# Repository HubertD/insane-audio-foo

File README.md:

insane-audio-foo
================

Portable Modular Digital Audio Mixer / Interface / Recorder with High Quality and stuff.

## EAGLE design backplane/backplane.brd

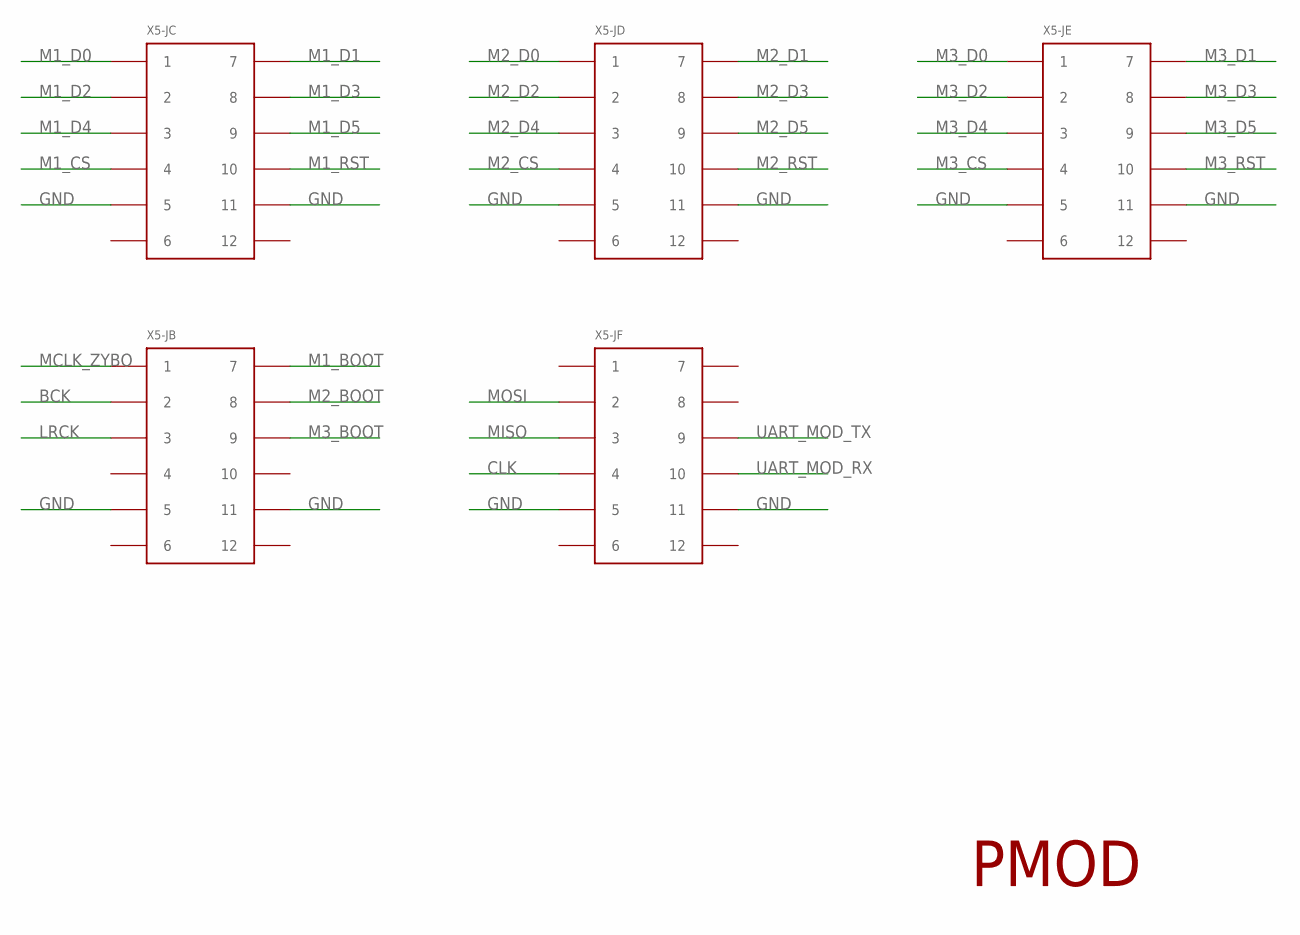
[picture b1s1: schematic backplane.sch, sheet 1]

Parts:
X5-JB, X5-JC, X5-JD, X5-JE, X5-JF: PINCON-2X6; PINCON-2X6-SMD

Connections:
BCK: X5-JB.P$2 (2); also elsewhere on the board
CLK: X5-JF.P$4 (4); also elsewhere on the board
GND: X5-JB.P$5 (5), X5-JB.P$11 (11), X5-JC.P$5 (5), X5-JC.P$11 (11), X5-JD.P$5 (5), X5-JD.P$11 (11), X5-JE.P$5 (5), X5-JE.P$11 (11), X5-JF.P$5 (5), X5-JF.P$11 (11); also elsewhere on the board
LRCK: X5-JB.P$3 (3); also elsewhere on the board
M1_BOOT: X5-JB.P$7 (7); also elsewhere on the board
M1_CS: X5-JC.P$4 (4); also elsewhere on the board
M1_D0: X5-JC.P$1 (1); also elsewhere on the board
M1_D1: X5-JC.P$7 (7); also elsewhere on the board
M1_D2: X5-JC.P$2 (2); also elsewhere on the board
M1_D3: X5-JC.P$8 (8); also elsewhere on the board
M1_D4: X5-JC.P$3 (3); also elsewhere on the board
M1_D5: X5-JC.P$9 (9); also elsewhere on the board
M1_RST: X5-JC.P$10 (10); also elsewhere on the board
M2_BOOT: X5-JB.P$8 (8); also elsewhere on the board
M2_CS: X5-JD.P$4 (4); also elsewhere on the board
M2_D0: X5-JD.P$1 (1); also elsewhere on the board
M2_D1: X5-JD.P$7 (7); also elsewhere on the board
M2_D2: X5-JD.P$2 (2); also elsewhere on the board
M2_D3: X5-JD.P$8 (8); also elsewhere on the board
M2_D4: X5-JD.P$3 (3); also elsewhere on the board
M2_D5: X5-JD.P$9 (9); also elsewhere on the board
M2_RST: X5-JD.P$10 (10); also elsewhere on the board
M3_BOOT: X5-JB.P$9 (9); also elsewhere on the board
M3_CS: X5-JE.P$4 (4); also elsewhere on the board
M3_D0: X5-JE.P$1 (1); also elsewhere on the board
M3_D1: X5-JE.P$7 (7); also elsewhere on the board
M3_D2: X5-JE.P$2 (2); also elsewhere on the board
M3_D3: X5-JE.P$8 (8); also elsewhere on the board
M3_D4: X5-JE.P$3 (3); also elsewhere on the board
M3_D5: X5-JE.P$9 (9); also elsewhere on the board
M3_RST: X5-JE.P$10 (10); also elsewhere on the board
MCLK_ZYBO: X5-JB.P$1 (1); also elsewhere on the board
MISO: X5-JF.P$3 (3); also elsewhere on the board
MOSI: X5-JF.P$2 (2); also elsewhere on the board
UART_MOD_RX: X5-JF.P$10 (10); also elsewhere on the board
UART_MOD_TX: X5-JF.P$9 (9); also elsewhere on the board

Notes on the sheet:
PMOD

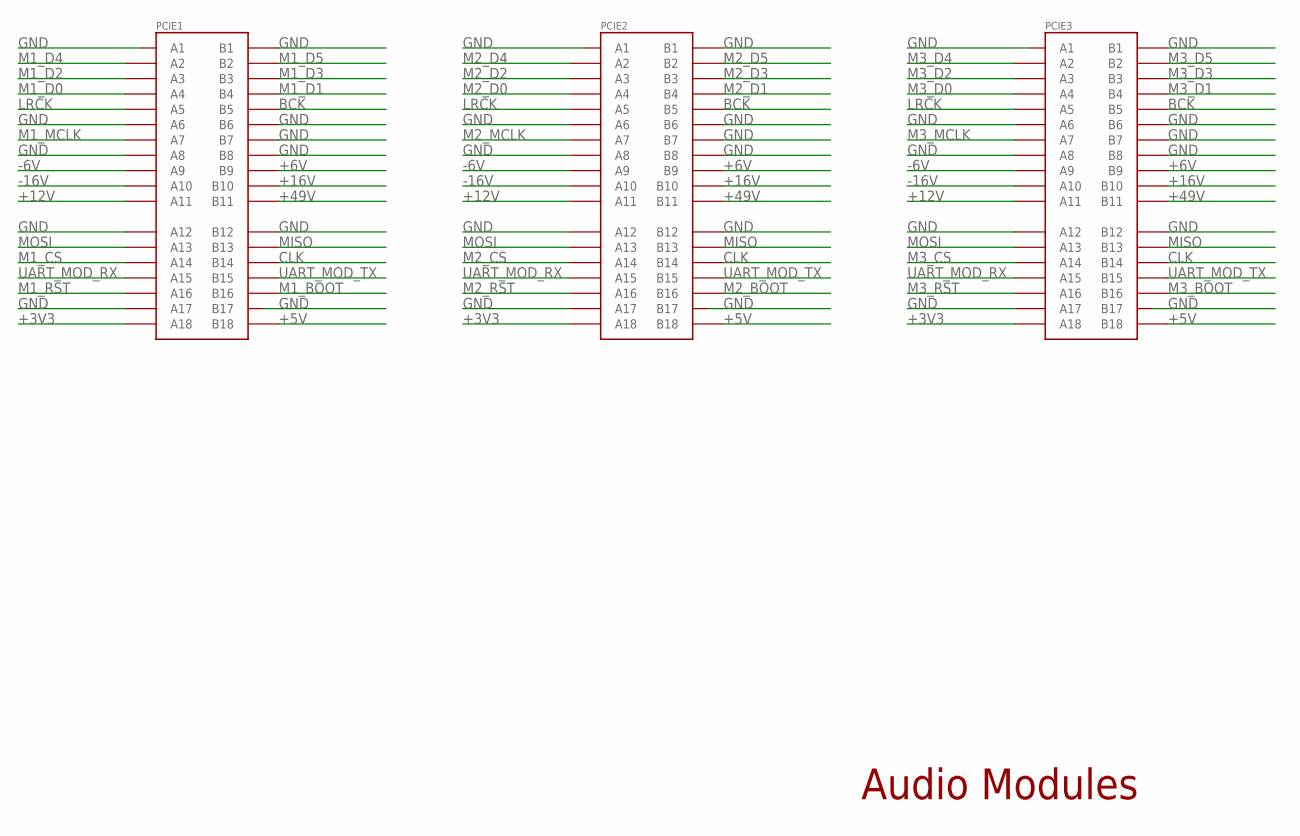
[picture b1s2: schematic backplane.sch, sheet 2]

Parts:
PCIE1, PCIE2, PCIE3: PCIE-36-SKT-SMD; FCI-10076266-100CLF

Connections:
+3V3: PCIE1.A18, PCIE2.A18, PCIE3.A18; also elsewhere on the board
+5V: PCIE1.B19 (B18), PCIE2.B19 (B18), PCIE3.B19 (B18); also elsewhere on the board
+6V: PCIE1.B9, PCIE2.B9, PCIE3.B9; also elsewhere on the board
+12V: PCIE1.A11, PCIE2.A11, PCIE3.A11; also elsewhere on the board
+16V: PCIE1.B10, PCIE2.B10, PCIE3.B10; also elsewhere on the board
+49V: PCIE1.B11, PCIE2.B11, PCIE3.B11; also elsewhere on the board
-6V: PCIE1.A9, PCIE2.A9, PCIE3.A9; also elsewhere on the board
-16V: PCIE1.A10, PCIE2.A10, PCIE3.A10; also elsewhere on the board
BCK: PCIE1.B5, PCIE2.B5, PCIE3.B5; also elsewhere on the board
CLK: PCIE1.B14, PCIE2.B14, PCIE3.B14; also elsewhere on the board
GND: PCIE1.A1, PCIE1.A6, PCIE1.A8, PCIE1.A12, PCIE1.A17, PCIE1.B1, PCIE1.B6, PCIE1.B7, PCIE1.B8, PCIE1.B12, PCIE1.B18 (B17), PCIE2.A1, PCIE2.A6, PCIE2.A8, PCIE2.A12, PCIE2.A17, PCIE2.B1, PCIE2.B6, PCIE2.B7, PCIE2.B8, PCIE2.B12, PCIE2.B18 (B17), PCIE3.A1, PCIE3.A6, PCIE3.A8, PCIE3.A12, PCIE3.A17, PCIE3.B1, PCIE3.B6, PCIE3.B7, PCIE3.B8, PCIE3.B12, PCIE3.B18 (B17); also elsewhere on the board
LRCK: PCIE1.A5, PCIE2.A5, PCIE3.A5; also elsewhere on the board
M1_BOOT: PCIE1.B16; also elsewhere on the board
M1_CS: PCIE1.A14; also elsewhere on the board
M1_D0: PCIE1.A4; also elsewhere on the board
M1_D1: PCIE1.B4; also elsewhere on the board
M1_D2: PCIE1.A3; also elsewhere on the board
M1_D3: PCIE1.B3; also elsewhere on the board
M1_D4: PCIE1.A2; also elsewhere on the board
M1_D5: PCIE1.B2; also elsewhere on the board
M1_MCLK: PCIE1.A7; also elsewhere on the board
M1_RST: PCIE1.A16; also elsewhere on the board
M2_BOOT: PCIE2.B16; also elsewhere on the board
M2_CS: PCIE2.A14; also elsewhere on the board
M2_D0: PCIE2.A4; also elsewhere on the board
M2_D1: PCIE2.B4; also elsewhere on the board
M2_D2: PCIE2.A3; also elsewhere on the board
M2_D3: PCIE2.B3; also elsewhere on the board
M2_D4: PCIE2.A2; also elsewhere on the board
M2_D5: PCIE2.B2; also elsewhere on the board
M2_MCLK: PCIE2.A7; also elsewhere on the board
M2_RST: PCIE2.A16; also elsewhere on the board
M3_BOOT: PCIE3.B16; also elsewhere on the board
M3_CS: PCIE3.A14; also elsewhere on the board
M3_D0: PCIE3.A4; also elsewhere on the board
M3_D1: PCIE3.B4; also elsewhere on the board
M3_D2: PCIE3.A3; also elsewhere on the board
M3_D3: PCIE3.B3; also elsewhere on the board
M3_D4: PCIE3.A2; also elsewhere on the board
M3_D5: PCIE3.B2; also elsewhere on the board
M3_MCLK: PCIE3.A7; also elsewhere on the board
M3_RST: PCIE3.A16; also elsewhere on the board
MISO: PCIE1.B13, PCIE2.B13, PCIE3.B13; also elsewhere on the board
MOSI: PCIE1.A13, PCIE2.A13, PCIE3.A13; also elsewhere on the board
UART_MOD_RX: PCIE1.A15, PCIE2.A15, PCIE3.A15; also elsewhere on the board
UART_MOD_TX: PCIE1.B15, PCIE2.B15, PCIE3.B15; also elsewhere on the board

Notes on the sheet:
Audio Modules

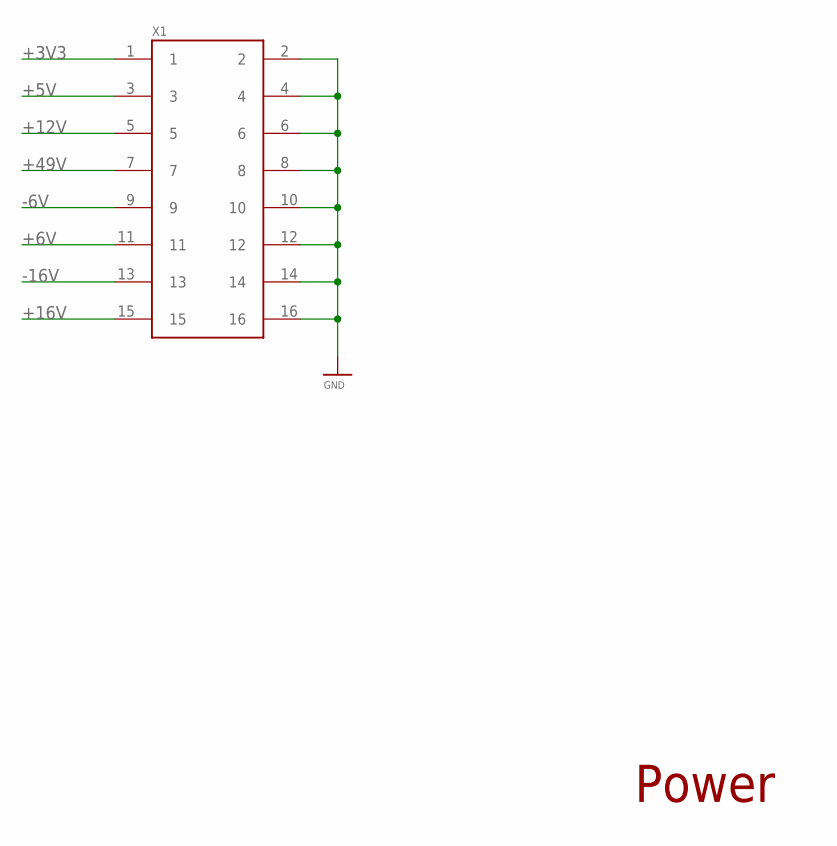
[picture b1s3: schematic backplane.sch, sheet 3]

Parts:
X1: PINCON-2X8

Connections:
+3V3: X1.1; also elsewhere on the board
+5V: X1.3; also elsewhere on the board
+6V: X1.11; also elsewhere on the board
+12V: X1.5; also elsewhere on the board
+16V: X1.15; also elsewhere on the board
+49V: X1.7; also elsewhere on the board
-6V: X1.9; also elsewhere on the board
-16V: X1.13; also elsewhere on the board
GND: X1.2, X1.4, X1.6, X1.8, X1.10, X1.12, X1.14, X1.16; also elsewhere on the board

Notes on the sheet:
Power

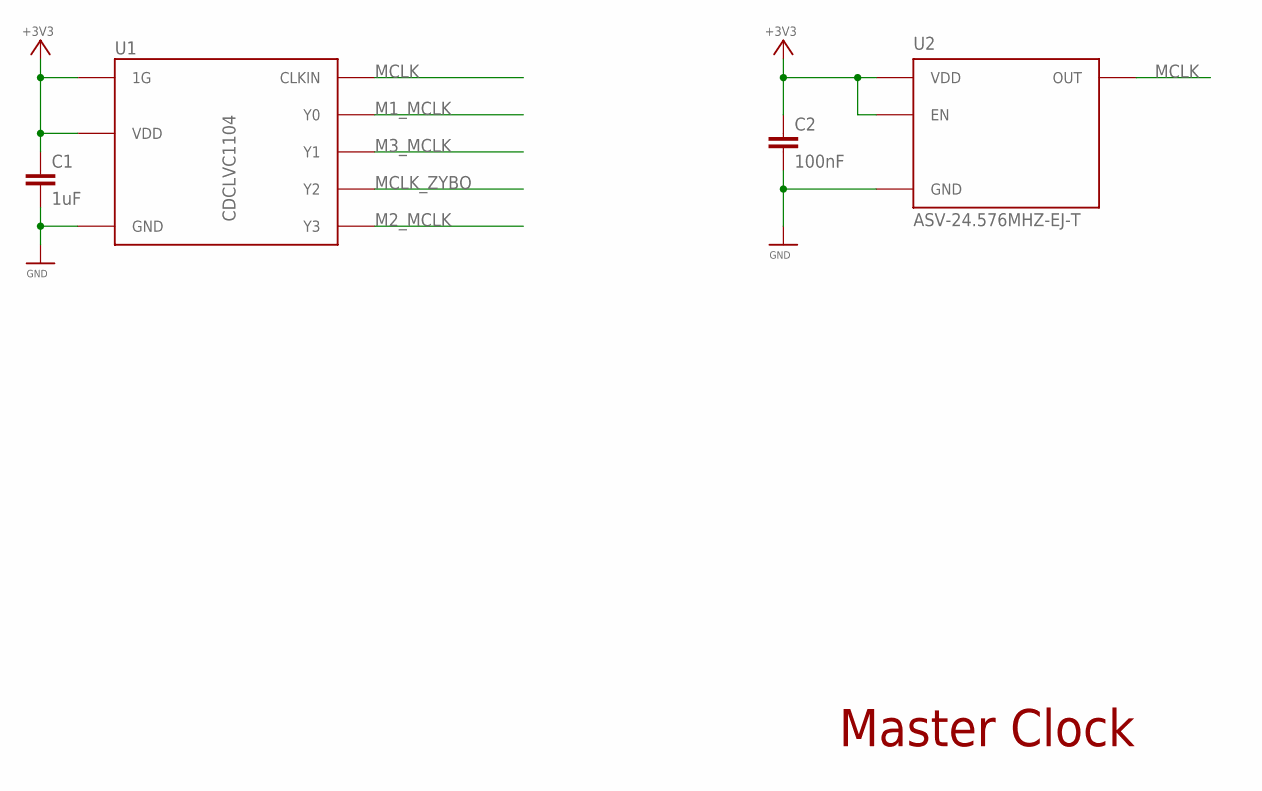
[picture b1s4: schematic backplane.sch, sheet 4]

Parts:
C1: 1uF; C0805
C2: 100nF; C0603
U1: CDCLVC1104; TSSOP8
U2: ASV-24.576MHZ-EJ-T; ABRACON_ASV; MPN ASV-24.576MHZ-EJ-T

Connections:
+3V3: C1.1, C2.1, U1.2 (1G), U1.6 (VDD), U2.1 (EN), U2.4 (VDD); also elsewhere on the board
GND: C1.2, C2.2, U1.4 (GND), U2.2 (GND); also elsewhere on the board
M1_MCLK: U1.3 (Y0); also elsewhere on the board
M2_MCLK: U1.7 (Y3); also elsewhere on the board
M3_MCLK: U1.8 (Y1); also elsewhere on the board
MCLK: U1.1 (CLKIN), U2.3 (OUT)
MCLK_ZYBO: U1.5 (Y2); also elsewhere on the board

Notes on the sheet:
Master Clock

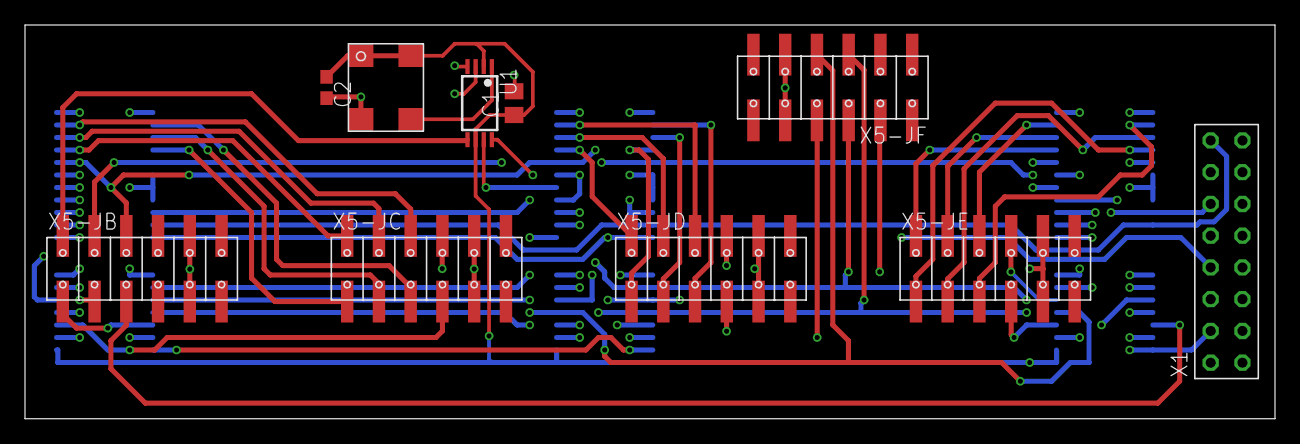
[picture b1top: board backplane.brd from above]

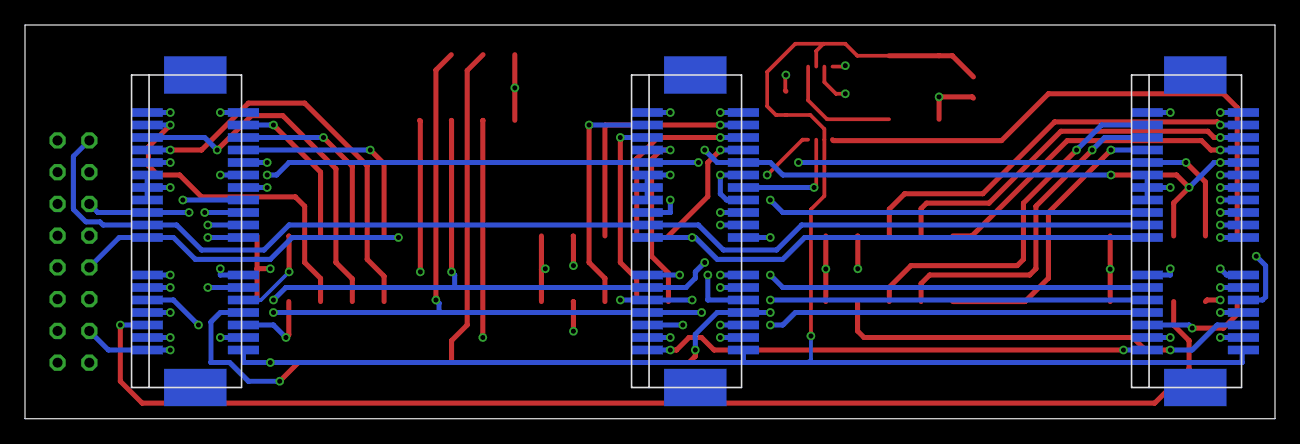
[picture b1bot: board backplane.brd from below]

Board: 4 copper layers, 100.0 x 31.5 mm, 13 parts (3 on the bottom side), 48 nets.

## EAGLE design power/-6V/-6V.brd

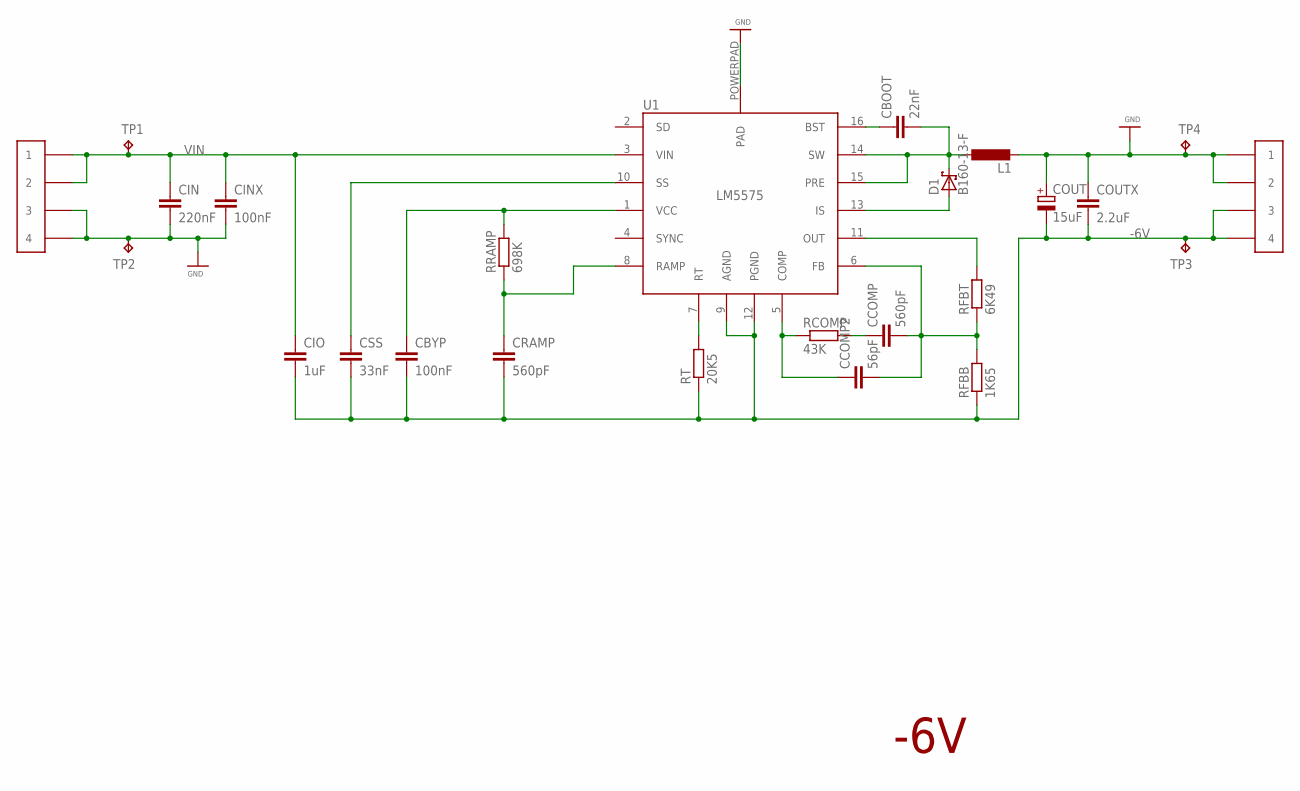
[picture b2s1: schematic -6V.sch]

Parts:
CBOOT: 22nF; C0603
CBYP: 100nF; C0603
CCOMP: 560pF; C0603
CCOMP2: 56pF; C0603
CIN: 220nF; C0805
CINX: 100nF; C0805
CIO: 1uF; C1206; MPN C3216X7R1H105K
COUT: 15uF; KEMET_EDK_5MM; MPN 10SVP15M
COUTX: 2.2uF; C0603; MPN GRM188R61A225KE34D
CRAMP: 560pF; C0603
CSS: 33nF; C0603
D1: B160-13-F; SMA
L1: LSDR1006; BOURNS-SDR1006; MPN SDR1006-560KL
RCOMP: 43K; R0603
RFBB: 1K65; R0603
RFBT: 6K49; R0603
RRAMP: 698K; R0603
RT: 20K5; R0603
TP1, TP2, TP3, TP4: TP; TESTPAD
U1: LM5575; HTSSOP16
X1, X2: PINCON-1X4

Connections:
-6V: CBYP.2, CIO.2, COUT.M (-), COUTX.2, CRAMP.2, CSS.2, RFBB.1, RT.1, TP3.P$1, U1.9 (AGND), U1.12 (PGND), X2.P$3 (3), X2.P$4 (4)
GND: CIN.2, CINX.2, COUT.P (+), COUTX.1, L1.2, TP2.P$1, TP4.P$1, U1.POWERPAD (PAD), X1.P$3 (3), X1.P$4 (4), X2.P$1 (1), X2.P$2 (2)
unnamed: CSS.1, U1.10 (SS)
unnamed: CBYP.1, RRAMP.2, U1.1 (VCC)
unnamed: CRAMP.1, RRAMP.1, U1.8 (RAMP)
unnamed: RT.2, U1.7 (RT)
unnamed: CCOMP2.1, RCOMP.1, U1.5 (COMP)
unnamed: CCOMP.1, RCOMP.2
unnamed: CCOMP.2, CCOMP2.2, RFBB.2, RFBT.1, U1.6 (FB)
unnamed: RFBT.2, U1.11 (OUT)
unnamed: D1.A, U1.13 (IS)
unnamed: CBOOT.2, D1.C, L1.1, U1.14 (SW), U1.15 (PRE)
unnamed: CBOOT.1, U1.16 (BST)
VIN: CIN.1, CINX.1, CIO.1, TP1.P$1, U1.3 (VIN), X1.P$1 (1), X1.P$2 (2)

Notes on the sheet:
-6V

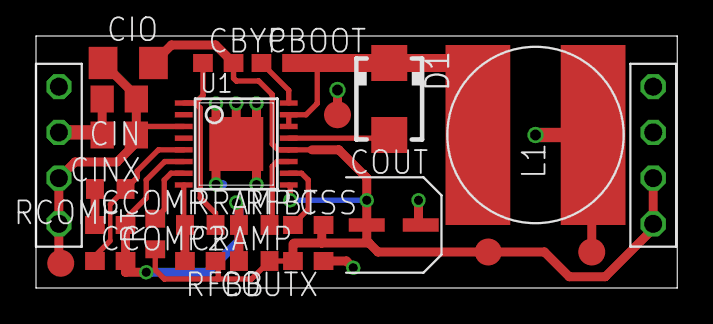
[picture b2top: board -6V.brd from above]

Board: 2 copper layers, 35.6 x 14.0 mm, 25 parts (0 on the bottom side), 14 nets.

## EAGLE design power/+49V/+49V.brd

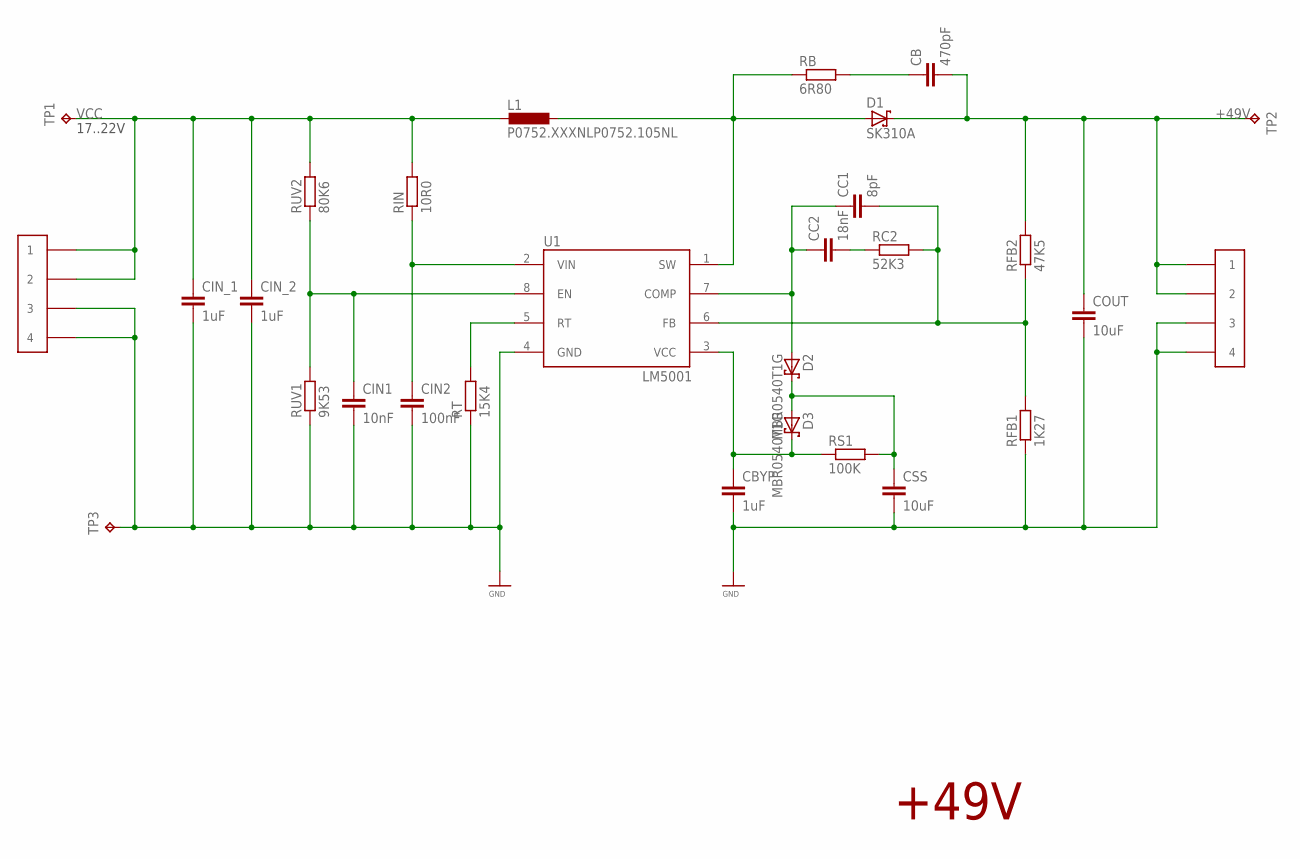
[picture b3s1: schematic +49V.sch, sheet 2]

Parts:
CB: 470pF; C0603
CBYP: 1uF; C0603; MPN GRM155R61A105KE15D
CC1: 8pF; C0805
CC2: 18nF; C0805
CIN1: 10nF; C0805; MPN GRM216R71H103KA01D
CIN2: 100nF; C0805; MPN C0805C104K5RACTU
CIN_1, CIN_2: 1uF; C1206; MPN C3216X7R1H105K160AB
COUT: 10uF; C2220K; MPN C5750X7S2A106M
CSS: 10uF; C0805; MPN LMK212BJ106KG-T
D1: SK310A; DO214AC
D2, D3: MBR0540T1G; SOD123
L1: P0752.XXXNLP0752.105NL; P0752.XXXNL
RB: 6R80; R0805; MPN RC0805FR-076R8L
RC2: 52K3; R0603
RFB1: 1K27; R0603
RFB2: 47K5; R0603
RIN: 10R0; R0603
RS1: 100K; R0603
RT: 15K4; R0603
RUV1: 9K53; R0603
RUV2: 80K6; R0603
TP1, TP2, TP3: TP; TESTPAD
U1: LM5001MAX; SOIC8
X1, X2: PINCON-1X4

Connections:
+49V: CB.2, COUT.1, D1.C, RFB2.2, TP2.P$1, X2.P$1 (1), X2.P$2 (2)
GND: CBYP.2, CIN1.2, CIN2.2, CIN_1.2, CIN_2.2, COUT.2, CSS.2, RFB1.1, RT.1, RUV1.1, TP3.P$1, U1.4 (GND), X1.P$3 (3), X1.P$4 (4), X2.P$3 (3), X2.P$4 (4)
unnamed: CBYP.1, D3.C, RS1.1, U1.3 (VCC)
unnamed: RT.2, U1.5 (RT)
unnamed: CIN2.1, RIN.1, U1.2 (VIN)
unnamed: CIN1.1, RUV1.2, RUV2.1, U1.8 (EN)
unnamed: D1.A, L1.P$1 (1), RB.1, U1.1 (SW)
unnamed: CB.1, RB.2
unnamed: CC1.1, CC2.1, D2.A, U1.7 (COMP)
unnamed: CC2.2, RC2.1
unnamed: CC1.2, RC2.2, RFB1.2, RFB2.1, U1.6 (FB)
unnamed: CSS.1, D2.C, D3.A, RS1.2
VCC: CIN_1.1, CIN_2.1, L1.P$2 (2), RIN.2, RUV2.2, TP1.P$1, X1.P$1 (1), X1.P$2 (2)

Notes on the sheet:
+49V
17..22V

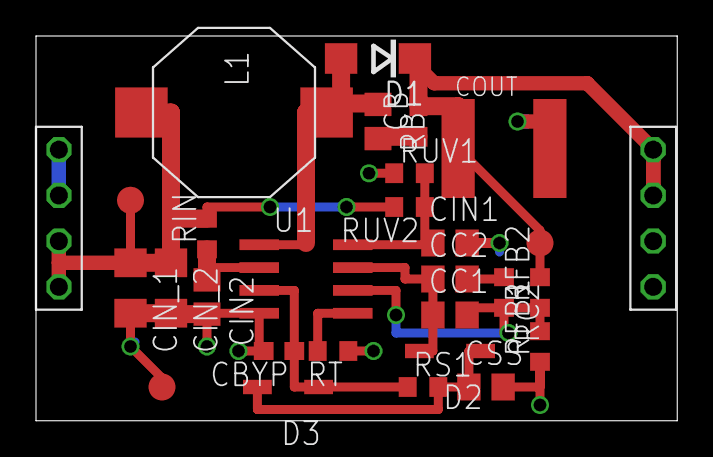
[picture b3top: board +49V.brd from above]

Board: 2 copper layers, 35.6 x 21.4 mm, 29 parts (0 on the bottom side), 13 nets.

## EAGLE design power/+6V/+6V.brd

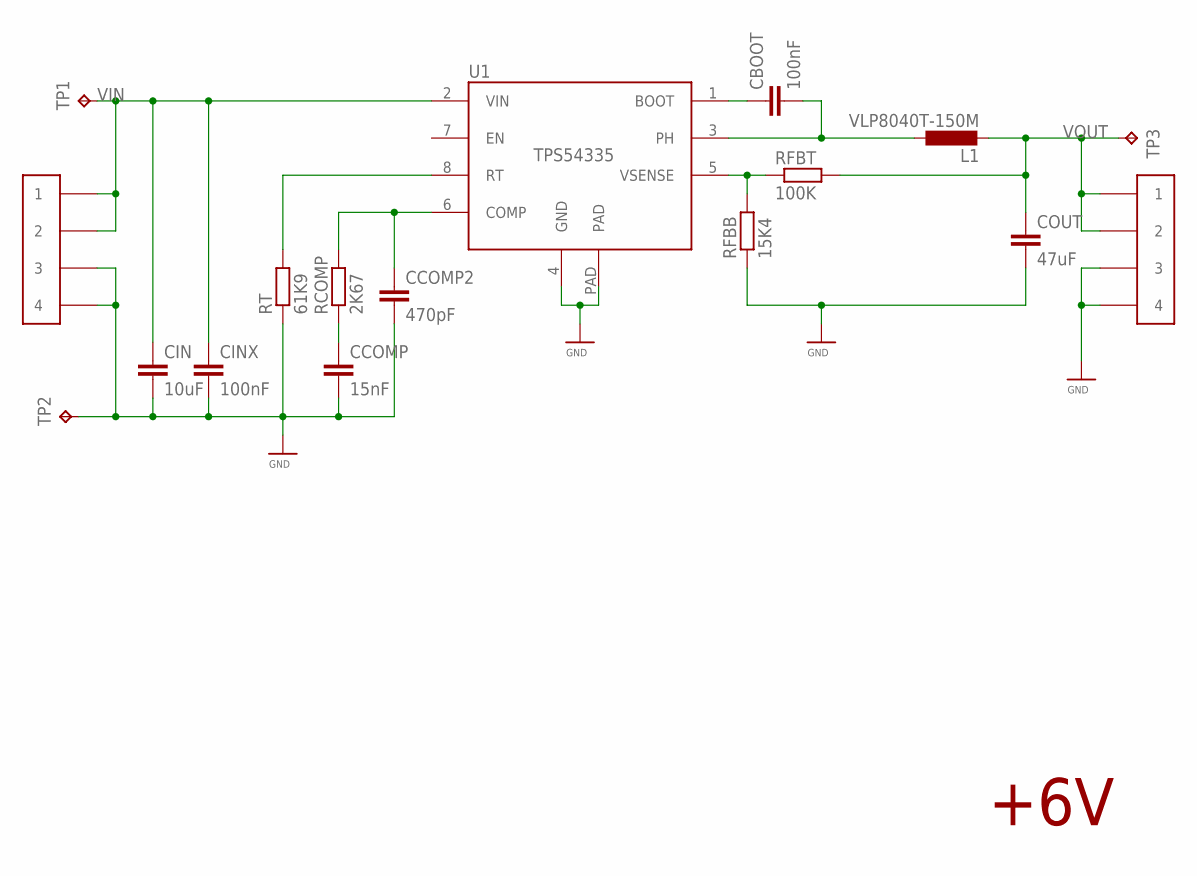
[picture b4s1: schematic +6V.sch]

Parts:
CBOOT: 100nF; C0603
CCOMP: 15nF; C0603
CCOMP2: 470pF; C0603
CIN: 10uF; C1210; MPN C3225X5R1E106K
CINX: 100nF; C0603
COUT: 47uF; C1812; MPN C4532X5R1A476M
L1: VLP8040T-150M; BOURNS-SDR1006
RCOMP: 2K67; R0603
RFBB: 15K4; R0603
RFBT: 100K; R0603
RT: 61K9; R0603
TP1, TP2, TP3: TP; TESTPAD
U1: TPS54335
X1, X2: PINCON-1X4

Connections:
GND: CCOMP.2, CCOMP2.2, CIN.2, CINX.2, COUT.2, RFBB.1, RT.1, TP2.P$1, U1.4 (GND), U1.PAD, X1.P$3 (3), X1.P$4 (4), X2.P$3 (3), X2.P$4 (4)
unnamed: RT.2, U1.8 (RT)
unnamed: CCOMP2.1, RCOMP.2, U1.6 (COMP)
unnamed: CCOMP.1, RCOMP.1
unnamed: CBOOT.2, L1.1, U1.3 (PH)
unnamed: CBOOT.1, U1.1 (BOOT)
unnamed: RFBB.2, RFBT.1, U1.5 (VSENSE)
VIN: CIN.1, CINX.1, TP1.P$1, U1.2 (VIN), X1.P$1 (1), X1.P$2 (2)
VOUT: COUT.1, L1.2, RFBT.2, TP3.P$1, X2.P$1 (1), X2.P$2 (2)

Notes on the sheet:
+6V

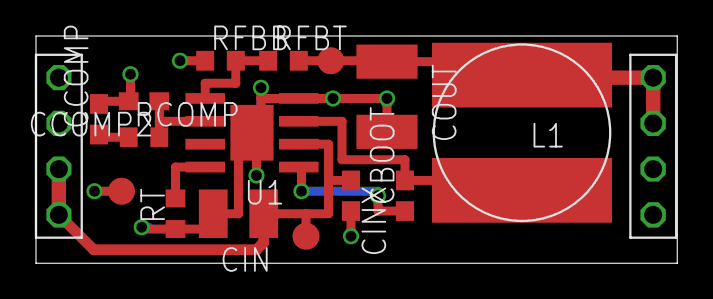
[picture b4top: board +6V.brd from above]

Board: 2 copper layers, 35.6 x 12.6 mm, 17 parts (0 on the bottom side), 9 nets.

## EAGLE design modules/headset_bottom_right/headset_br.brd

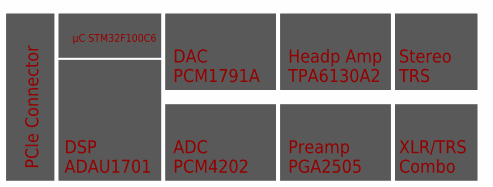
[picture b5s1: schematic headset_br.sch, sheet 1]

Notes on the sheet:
PCIe Connector
DSP ADAU1701
µC STM32F100C6
ADC PCM4202
Preamp PGA2505
DAC PCM1791A
Headp Amp TPA6130A2
Stereo TRS
XLR/TRS Combo

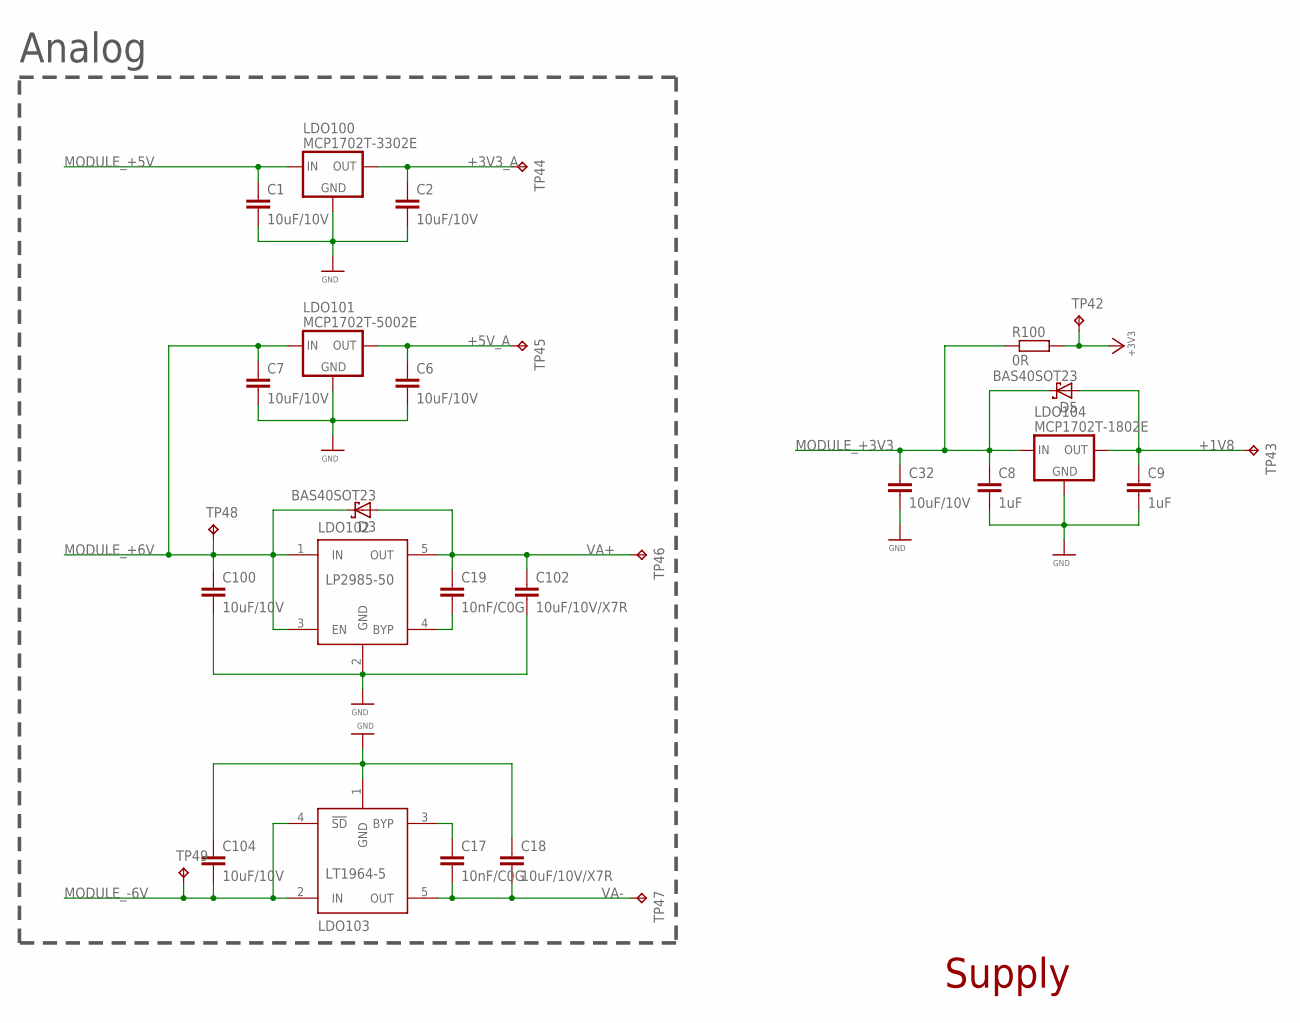
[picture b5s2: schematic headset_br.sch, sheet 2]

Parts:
C1, C2, C6, C7: 10uF/10V; C0805; MPN CC0805ZKY5V6BB106
C8, C9: 1uF; C0603; MPN C1608X7R1C105K080AC
C17, C19: 10nF/C0G; C0603; MPN C1608C0G1H103J080AA
C18, C102: 10uF/10V/X7R; C0805; MPN C2012X7R1A106K125AC
C32, C100, C104: 10uF/10V; C0805; MPN C2012X7R1A106K125AC
D3, D5: BAS40SOT23; SOT23
LDO100: MCP1702T-3302E; SOT23; MPN MCP1702T-3302E/CB
LDO101: MCP1702T-5002E; SOT23; MPN MCP1702T-5002E/CB
LDO102: LP2985-50; SOT23-5; MPN LP2985-50DBVR
LDO103: LT1964-5; SOT23-5; MPN LT1964ES5-5#TRMPBF
LDO104: MCP1702T-1802E; SOT23; MPN MCP1702T-1802E/CB
R100: 0R; R0603
TP42, TP43, TP44, TP45, TP46, TP47, TP48, TP49: TPS; TESTPAD_SMALL

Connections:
+1V8: C9.1, D5.1 (A), LDO104.2 (OUT), TP43.P$1; also elsewhere on the board
+3V3: R100.2, TP42.P$1; also elsewhere on the board
+3V3_A: C2.1, LDO100.2 (OUT), TP44.P$1; also elsewhere on the board
+5V_A: C6.1, LDO101.2 (OUT), TP45.P$1; also elsewhere on the board
GND: C1.2, C2.2, C6.2, C7.2, C8.2, C9.2, C18.1, C32.2, C100.2, C102.2, C104.1, LDO100.1 (GND), LDO101.1 (GND), LDO102.2 (GND), LDO103.1 (GND), LDO104.1 (GND); also elsewhere on the board
MODULE_+3V3: C8.1, C32.1, D5.3 (C), LDO104.3 (IN), R100.1; also elsewhere on the board
MODULE_+5V: C1.1, LDO100.3 (IN); also elsewhere on the board
MODULE_+6V: C7.1, C100.1, D3.3 (C), LDO101.3 (IN), LDO102.1 (IN), LDO102.3 (EN), TP48.P$1; also elsewhere on the board
MODULE_-6V: C104.2, LDO103.2 (IN), LDO103.4 (!SD), TP49.P$1; also elsewhere on the board
unnamed: C17.1, LDO103.3 (BYP)
unnamed: C19.2, LDO102.4 (BYP)
VA+: C19.1, C102.1, D3.1 (A), LDO102.5 (OUT), TP46.P$1; also elsewhere on the board
VA-: C17.2, C18.2, LDO103.5 (OUT), TP47.P$1; also elsewhere on the board

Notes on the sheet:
Supply
Analog

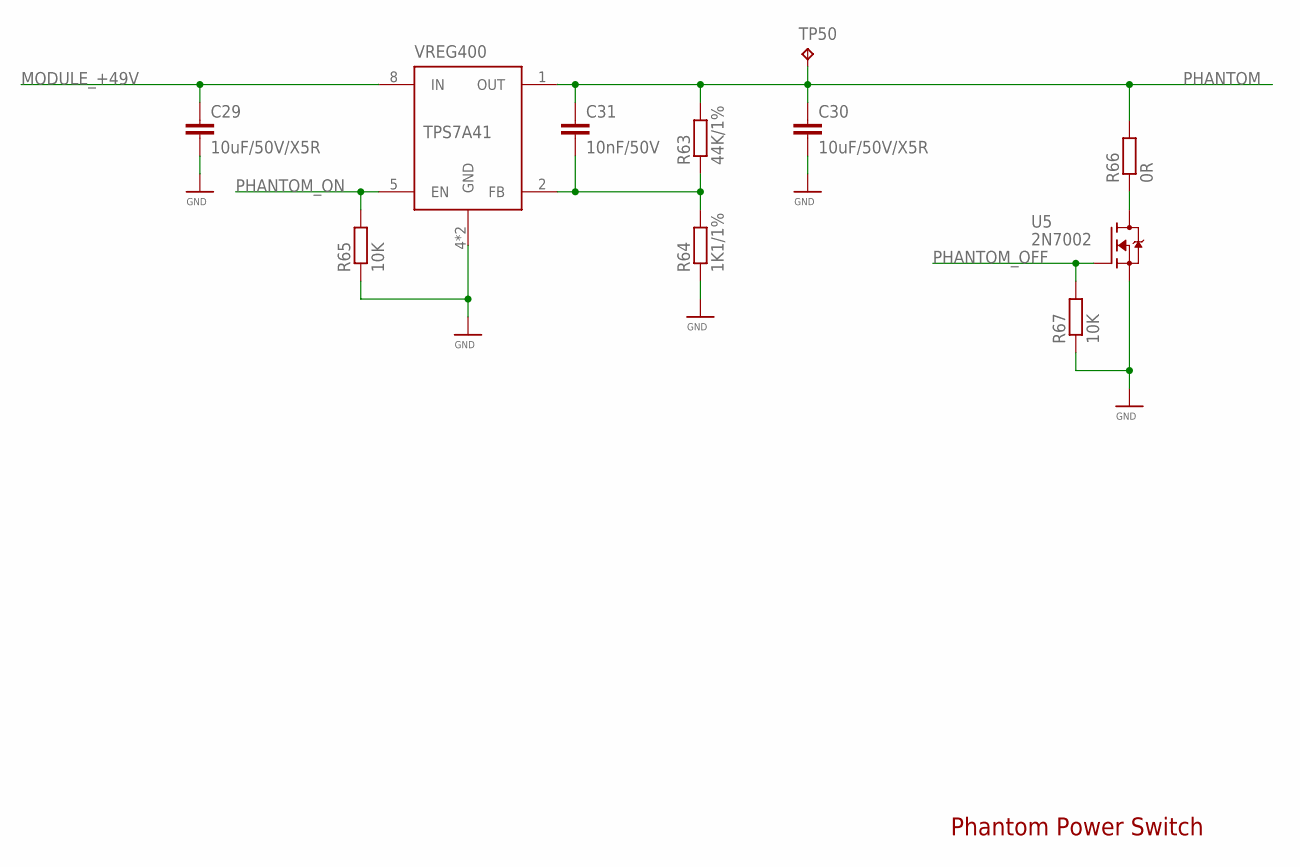
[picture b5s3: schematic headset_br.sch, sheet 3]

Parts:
C29, C30: 10uF/50V/X5R; C1206; MPN GRM31CR61H106KA12L
C31: 10nF/50V; C0603; MPN C1608C0G1H103J080AA
R63: 44K/1%; R0603; MPN ERJ-3EKF4422V
R64: 1K1/1%; R0603; MPN ERJ-3EKF1101V
R65, R67: 10K; R0603; MPN ERJ-3EKF1002V
R66: 0R; R0603
TP50: TPS; TESTPAD_SMALL
U5: 2N7002; SOT23
VREG400: TPS7A41

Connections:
GND: C29.2, C30.2, R64.1, R65.1, R67.1, U5.2 (S), VREG400.4 (GND), VREG400.POWERPAD (GND); also elsewhere on the board
MODULE_+49V: C29.1, VREG400.8 (IN); also elsewhere on the board
unnamed: C31.2, R63.1, R64.2, VREG400.2 (FB)
unnamed: R66.1, U5.3 (D)
PHANTOM: C30.1, C31.1, R63.2, R66.2, TP50.P$1, VREG400.1 (OUT); also elsewhere on the board
PHANTOM_OFF: R67.2, U5.1 (G); also elsewhere on the board
PHANTOM_ON: R65.2, VREG400.5 (EN); also elsewhere on the board

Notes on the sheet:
Phantom Power Switch

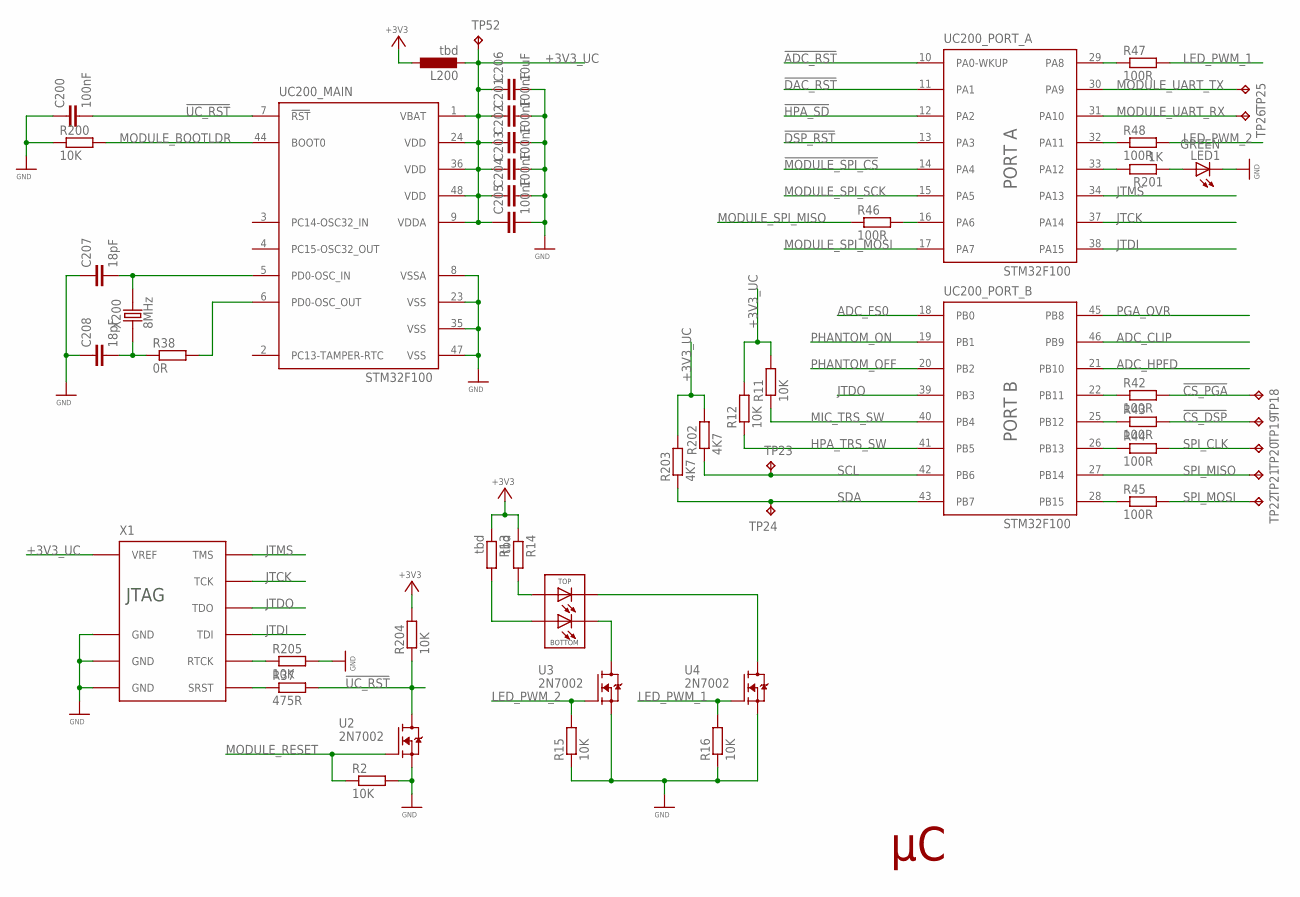
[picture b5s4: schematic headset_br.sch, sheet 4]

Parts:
C200, C201, C202, C203, C204, C205: 100nF; C0603; MPN 0603YC104KAT2A
C206: 10uF; C0805; MPN C2012X7R1A106K125AC
C207, C208: 18pF; C0603; MPN C0603C180J5GACTU
DUOLED: MENTOR-2LEDRED/GREEN; MENTOR-2LED
L200: tbd; R0805
LED1: GREEN; CHIP-LED0603
R2, R11, R12, R15, R16, R200, R204, R205: 10K; R0603; MPN ERJ-3EKF1002V
R13, R14: tbd; R0603
R37: 475R; R0603; MPN ERJ-3EKF4750V
R38: 0R; R0603
R42, R43, R44, R45, R46, R47, R48: 100R; R0603; MPN ERJ-3EKF1000V
R201: 1K; R0603; MPN CRCW06031K00FKEA
R202, R203: 4K7; R0603; MPN ERJ-3EKF4701V
TP18, TP19, TP20, TP21, TP22, TP23, TP24, TP25, TP26, TP52: TPS; TESTPAD_SMALL
U2, U3, U4: 2N7002; SOT23
UC200: STM32F100XXLQFP48; LQFP48; MPN STM32F100C8T6B
X1: JTAG; FTS-105-01-X-DV
X200: 8MHz; ABRACON_ABM7; MPN ABM7-8.000MHZ-D2Y-T

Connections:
!ADC_RST: UC200.10 (PA0-WKUP); also elsewhere on the board
!CS_DSP: R43.2, TP19.P$1; also elsewhere on the board
!CS_PGA: R42.2, TP18.P$1; also elsewhere on the board
!DAC_RST: UC200.11 (PA1); also elsewhere on the board
!DSP_RST: UC200.13 (PA3); also elsewhere on the board
!HPA_SD: UC200.12 (PA2); also elsewhere on the board
!MODULE_SPI_CS: UC200.14 (PA4); also elsewhere on the board
!UC_RST: C200.2, R37.2, R204.1, U2.3 (D), UC200.7 (!RST)
+3V3: L200.1, R13.1, R14.1, R204.2; also elsewhere on the board
+3V3_UC: C201.1, C202.1, C203.1, C204.1, C205.1, C206.1, L200.2, R11.2, R12.2, R202.2, R203.2, TP52.P$1, UC200.1 (VBAT), UC200.9 (VDDA), UC200.24 (VDD), UC200.36 (VDD), UC200.48 (VDD), X1.1 (VREF)
ADC_CLIP: UC200.46 (PB9); also elsewhere on the board
ADC_FS0: UC200.18 (PB0); also elsewhere on the board
ADC_HPFD: UC200.21 (PB10); also elsewhere on the board
GND: C200.1, C201.2, C202.2, C203.2, C204.2, C205.2, C206.2, C207.1, C208.1, LED1.C, R2.2, R15.1, R16.1, R200.1, R205.2, U2.2 (S), U3.2 (S), U4.2 (S), UC200.8 (VSSA), UC200.23 (VSS), UC200.35 (VSS), UC200.47 (VSS), X1.3 (GND), X1.5 (GND), X1.9 (GND); also elsewhere on the board
HPA_TRS_SW: R12.1, UC200.41 (PB5); also elsewhere on the board
JTCK: UC200.37 (PA14), X1.4 (TCK)
JTDI: UC200.38 (PA15), X1.8 (TDI)
JTDO: UC200.39 (PB3), X1.6 (TDO)
JTMS: UC200.34 (PA13), X1.2 (TMS)
LED_PWM_1: R16.2, R47.2, U4.1 (G)
LED_PWM_2: R15.2, R48.2, U3.1 (G)
MIC_TRS_SW: R11.1, UC200.40 (PB4); also elsewhere on the board
MODULE_BOOTLDR: R200.2, UC200.44 (BOOT0); also elsewhere on the board
MODULE_RESET: R2.1, U2.1 (G); also elsewhere on the board
MODULE_SPI_MISO: R46.1; also elsewhere on the board
MODULE_SPI_MOSI: UC200.17 (PA7); also elsewhere on the board
MODULE_SPI_SCK: UC200.15 (PA5); also elsewhere on the board
MODULE_UART_RX: TP26.P$1, UC200.31 (PA10); also elsewhere on the board
MODULE_UART_TX: TP25.P$1, UC200.30 (PA9); also elsewhere on the board
unnamed: R205.1, X1.7 (RTCK)
unnamed: LED1.A, R201.1
unnamed: R201.2, UC200.33 (PA12)
unnamed: C207.2, UC200.5 (PD0-OSC_IN), X200.P$2 (2)
unnamed: R38.2, UC200.6 (PD0-OSC_OUT)
unnamed: DUOLED.A_BOTTOM, R13.2
unnamed: DUOLED.A_TOP, R14.2
unnamed: DUOLED.C_BOTTOM, U3.3 (D)
unnamed: DUOLED.C_TOP, U4.3 (D)
unnamed: R37.1, X1.10 (SRST)
unnamed: C208.2, R38.1, X200.P$1 (1)
unnamed: R42.1, UC200.22 (PB11)
unnamed: R43.1, UC200.25 (PB12)
unnamed: R44.1, UC200.26 (PB13)
unnamed: R45.1, UC200.28 (PB15)
unnamed: R46.2, UC200.16 (PA6)
unnamed: R48.1, UC200.32 (PA11)
unnamed: R47.1, UC200.29 (PA8)
PGA_OVR: UC200.45 (PB8); also elsewhere on the board
PHANTOM_OFF: UC200.20 (PB2); also elsewhere on the board
PHANTOM_ON: UC200.19 (PB1); also elsewhere on the board
SCL: R202.1, TP23.P$1, UC200.42 (PB6); also elsewhere on the board
SDA: R203.1, TP24.P$1, UC200.43 (PB7); also elsewhere on the board
SPI_CLK: R44.2, TP20.P$1; also elsewhere on the board
SPI_MISO: TP21.P$1, UC200.27 (PB14); also elsewhere on the board
SPI_MOSI: R45.2, TP22.P$1; also elsewhere on the board
